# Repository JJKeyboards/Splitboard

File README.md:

# Splitboard
 30% Splitkeyboard

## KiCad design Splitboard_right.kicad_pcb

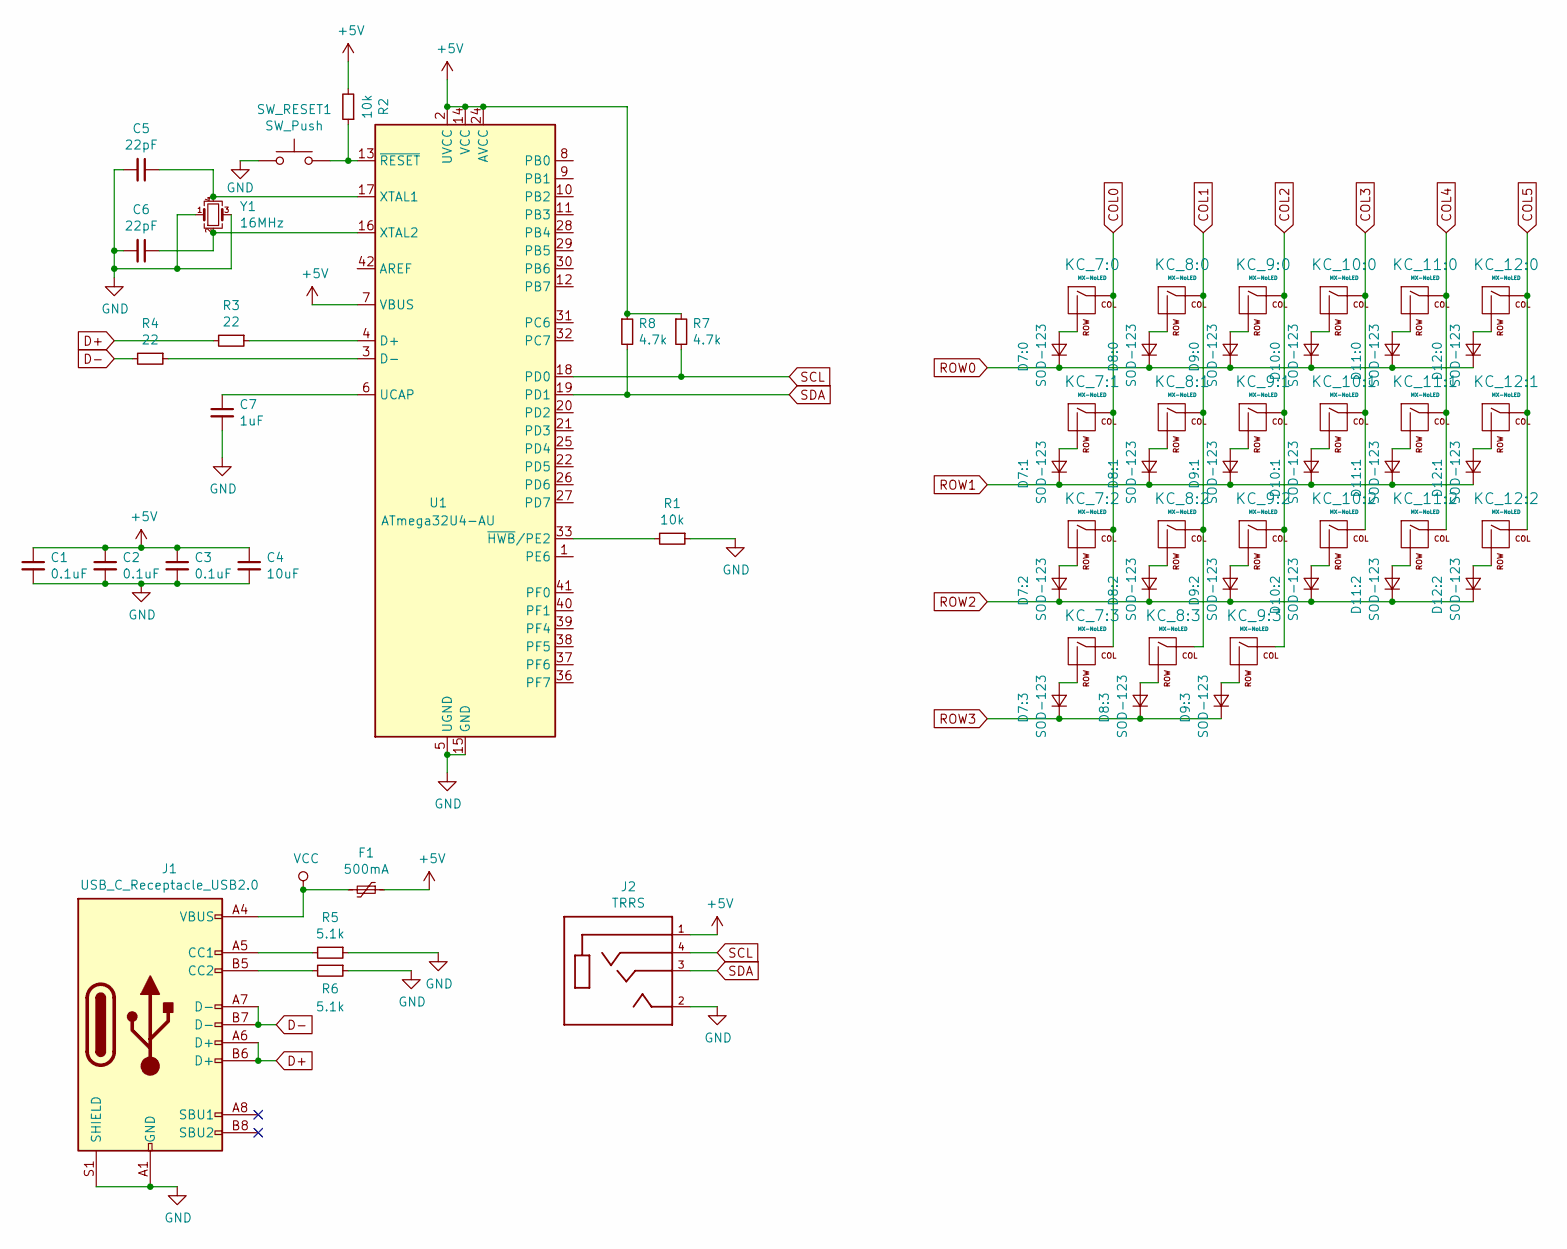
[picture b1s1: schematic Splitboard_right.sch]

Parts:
C1, C2, C3: 0.1uF; C_0805_2012Metric_Pad1.15x1.40mm_HandSolder
C4: 10uF; C_0805_2012Metric_Pad1.15x1.40mm_HandSolder
C5, C6: 22pF; C_0805_2012Metric_Pad1.15x1.40mm_HandSolder
C7: 1uF; C_0805_2012Metric_Pad1.15x1.40mm_HandSolder
D7:0, D7:1, D7:2, D7:3, D8:0, D8:1, D8:2, D8:3, D9:0, D9:1, D9:2, D9:3, D10:0, D10:1, D10:2, D11:0, D11:1, D11:2, D12:0, D12:1, D12:2: SOD-123; D_0805_2012Metric_Pad1.15x1.40mm_HandSolder
F1: 500mA; Fuse_1206_3216Metric_Pad1.42x1.75mm_HandSolder
J1: USB_C_Receptacle_USB2.0; USB_C_Receptacle_JAE_DX07S016JA1
J2: TRRS; CUI_SJ-43514-SMT
KC_7:0, KC_7:1, KC_7:2, KC_7:3, KC_8:0, KC_8:1, KC_8:2, KC_8:3, KC_9:0, KC_9:1, KC_9:2, KC_9:3, KC_10:0, KC_10:1, KC_10:2, KC_11:0, KC_11:1, KC_11:2, KC_12:0, KC_12:1, KC_12:2: MX-NoLED; MXOnly-1U-NoLED
R1, R2: 10k; R_0805_2012Metric_Pad1.15x1.40mm_HandSolder
R3, R4: 22; R_0805_2012Metric_Pad1.15x1.40mm_HandSolder
R5, R6: 5.1k; R_0805_2012Metric_Pad1.15x1.40mm_HandSolder
R7, R8: 4.7k; R_0805_2012Metric_Pad1.15x1.40mm_HandSolder
SW_RESET1: SW_Push; SW_SPST_TL3342
U1: ATmega32U4-AU; TQFP-44_10x10mm_P0.8mm
Y1: 16MHz; Crystal_SMD_3225-4Pin_3.2x2.5mm_HandSoldering

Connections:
+5V: C1.1, C2.1, C3.1, C4.1, F1.1, J2.1, R2.2, R7.1, R8.1, U1.2 (UVCC), U1.7 (VBUS), U1.14 (VCC), U1.24 (AVCC), U1.34 (VCC), U1.44 (AVCC)
COL0: KC_7:0.1 (COL), KC_7:1.1 (COL), KC_7:2.1 (COL), KC_7:3.1 (COL)
COL1: KC_8:0.1 (COL), KC_8:1.1 (COL), KC_8:2.1 (COL), KC_8:3.1 (COL)
COL2: KC_9:0.1 (COL), KC_9:1.1 (COL), KC_9:2.1 (COL), KC_9:3.1 (COL)
COL3: KC_10:0.1 (COL), KC_10:1.1 (COL), KC_10:2.1 (COL)
COL4: KC_11:0.1 (COL), KC_11:1.1 (COL), KC_11:2.1 (COL)
COL5: KC_12:0.1 (COL), KC_12:1.1 (COL), KC_12:2.1 (COL)
D+: J1.A6 (D+), J1.B6 (D+), R3.2
D-: J1.A7 (D-), J1.B7 (D-), R4.2
GND: C1.2, C2.2, C3.2, C4.2, C5.2, C6.2, C7.2, J1.A1 (GND), J1.A12 (GND), J1.B1 (GND), J1.B12 (GND), J1.S1 (SHIELD), J2.2, R1.1, R5.1, R6.1, SW_RESET1.1, U1.5 (UGND), U1.15 (GND), U1.23 (GND), U1.35 (GND), U1.43 (GND), Y1.1, Y1.3
unnamed: C5.1, U1.17 (XTAL1), Y1.4
unnamed: C6.1, U1.16 (XTAL2), Y1.2
unnamed: C7.1, U1.6 (UCAP)
unnamed: D7:0.2 (A), KC_7:0.2 (ROW)
unnamed: D7:1.2 (A), KC_7:1.2 (ROW)
unnamed: D7:2.2 (A), KC_7:2.2 (ROW)
unnamed: D7:3.2 (A), KC_7:3.2 (ROW)
unnamed: D8:0.2 (A), KC_8:0.2 (ROW)
unnamed: D8:1.2 (A), KC_8:1.2 (ROW)
unnamed: D8:2.2 (A), KC_8:2.2 (ROW)
unnamed: D8:3.2 (A), KC_8:3.2 (ROW)
unnamed: D9:0.2 (A), KC_9:0.2 (ROW)
unnamed: D9:1.2 (A), KC_9:1.2 (ROW)
unnamed: D9:2.2 (A), KC_9:2.2 (ROW)
unnamed: D9:3.2 (A), KC_9:3.2 (ROW)
unnamed: D10:0.2 (A), KC_10:0.2 (ROW)
unnamed: D10:1.2 (A), KC_10:1.2 (ROW)
unnamed: D10:2.2 (A), KC_10:2.2 (ROW)
unnamed: D11:0.2 (A), KC_11:0.2 (ROW)
unnamed: D11:1.2 (A), KC_11:1.2 (ROW)
unnamed: D11:2.2 (A), KC_11:2.2 (ROW)
unnamed: D12:0.2 (A), KC_12:0.2 (ROW)
unnamed: D12:1.2 (A), KC_12:1.2 (ROW)
unnamed: D12:2.2 (A), KC_12:2.2 (ROW)
unnamed: J1.A5 (CC1), R5.2
unnamed: J1.B5 (CC2), R6.2
unnamed: R1.2, U1.33 (~HWB~/PE2)
unnamed: R2.1, SW_RESET1.2, U1.13 (~RESET)
unnamed: R3.1, U1.4 (D+)
unnamed: R4.1, U1.3 (D-)
ROW0: D7:0.1 (K), D8:0.1 (K), D9:0.1 (K), D10:0.1 (K), D11:0.1 (K), D12:0.1 (K)
ROW1: D7:1.1 (K), D8:1.1 (K), D9:1.1 (K), D10:1.1 (K), D11:1.1 (K), D12:1.1 (K)
ROW2: D7:2.1 (K), D8:2.1 (K), D9:2.1 (K), D10:2.1 (K), D11:2.1 (K), D12:2.1 (K)
ROW3: D7:3.1 (K), D8:3.1 (K), D9:3.1 (K)
SCL: J2.4, R7.2, U1.18 (PD0)
SDA: J2.3, R8.2, U1.19 (PD1)
VCC: F1.2, J1.A4 (VBUS), J1.A9 (VBUS), J1.B4 (VBUS), J1.B9 (VBUS)

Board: 2 copper layers, 63 parts (0 on the bottom side), 47 nets, no tracks yet.

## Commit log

2020-08-31 First initialization
2020-08-31 Add submodules
2020-08-31 libs and footprints
2020-08-31 save
2020-08-31 save.1
2020-08-31 basic layout no switches
2020-08-31 left side switch layout
2020-08-31 schematic done
2020-08-31 reupload last save today
2020-09-02 pcb update
